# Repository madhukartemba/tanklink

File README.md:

# TankLink

Local rooftop **tank ↔ pump** control — no cloud required.

- **Phone ↔ pump:** BLE (claim/pair, On/Off, settings)
- **Tank ↔ pump:** LoRa (RA-02 / SX1278) — tank TX + pump RX done
- **Hardware:** ESP32-C3 (pump + tank), Flutter app

| Folder | Role |
| --- | --- |
| [`pump_node/`](pump_node/) | ESP32-C3 SuperMini pump (BLE GATT, starter relays, LoRa RX, schedules) |
| [`tank_node/`](tank_node/) | XIAO ESP32-C3 tank sensor (floats, LoRa TX, deep sleep) |
| [`tanklink_app/`](tanklink_app/) | Flutter app — multi-pump, slide-to-start, settings, schedules, in-app updates |
| [`components/tanklink_lora/`](components/tanklink_lora/) | Shared SX1278 driver and LoRa packet format |

**Pin maps (both boards):** [`docs/PINMAPS.md`](docs/PINMAPS.md)  
**BLE + LoRa byte layouts:** [`docs/PROTOCOL.md`](docs/PROTOCOL.md)  
**Build and flash:** [`docs/firmware-build-setup.md`](docs/firmware-build-setup.md)  
**Settings and pins to change:** [`docs/CONFIGURATION.md`](docs/CONFIGURATION.md)  
**Working on this repo with an agent:** [`AGENTS.md`](AGENTS.md)  
**Tank LED error codes:** [`docs/ERROR_CODES.md`](docs/ERROR_CODES.md)

## Quick start

### Firmware (ESP-IDF)

Built with **ESP-IDF v6.1.0** (tag [`v6.1`](https://github.com/espressif/esp-idf/releases/tag/v6.1), commit `fff9895c`). New computer? Follow [`docs/firmware-build-setup.md`](docs/firmware-build-setup.md). To change pins or timings, see [`docs/CONFIGURATION.md`](docs/CONFIGURATION.md).

```bash
. "$HOME/esp/esp-idf/export.sh"
cd pump_node
idf.py set-target esp32c3
idf.py build
idf.py -p /dev/cu.usbmodemXXXX flash monitor
```

Hold the pump **button** ~5 s to enter BLE pairing. Advertise name is `TankLink-XXXX` (MAC suffix).

After adding the pump in the app, set **Starter → two-button**. A new or factory-reset pump defaults to "none" and won't pulse the relays.

`idf.py erase-flash` clears NVS pairing.

See [`pump_node/README.md`](pump_node/README.md) for GATT notes.

### App (Flutter)

Flutter 3.50, JDK 17, Android SDK. See [`docs/firmware-build-setup.md`](docs/firmware-build-setup.md#8-build-the-app).

```bash
cd tanklink_app
flutter pub get
flutter run
```

## Firmware updates (BLE OTA)

Pump firmware can be updated from the app over BLE (dual OTA partitions).

1. Bump `TANKLINK_FW_VERSION` and build `pump_node`
2. Publish a GitHub release tagged `pump-vX.Y.Z` with `pump_node.bin` + `firmware-manifest.json`
3. See [`docs/firmware-release.md`](docs/firmware-release.md) and `./scripts/make_pump_manifest.sh`

First flash after the OTA partition change must be over **USB**. Later updates use the app.

## Status (high level)

- [x] BLE claim / auth / multi-pump
- [x] Pump On/Off + auto-off + buzzer settings
- [x] NeoPixel status + slide-to-start UI
- [x] BLE OTA + GitHub Releases check
- [x] Starter relays (GPIO0/1, active-low) + single button
- [x] Tank node floats + LoRa TX + deep sleep / heartbeat
- [x] Pump LoRa RX + tank auto-pair (app → BLE → LoRa PAIR)
- [x] Daily fill schedules (clock set from the phone)
- [x] Second float: almost-empty sensor or a second tank
- [x] Up to 4 tank sensors per pump (up to 8 tanks), one selected tank filled at a time
- [x] DS3231 RTC: schedules and the tank's last-seen time survive a restart
- [x] Tank solar: 5 V panel on VIN charges the LiPo through the XIAO charger; the app shows the battery trend
- [x] Fill history: the last 200 fills, how long each took and why it stopped
- [x] Fill when low (both floats) and water and power charts

## License

Private / personal use unless otherwise noted.

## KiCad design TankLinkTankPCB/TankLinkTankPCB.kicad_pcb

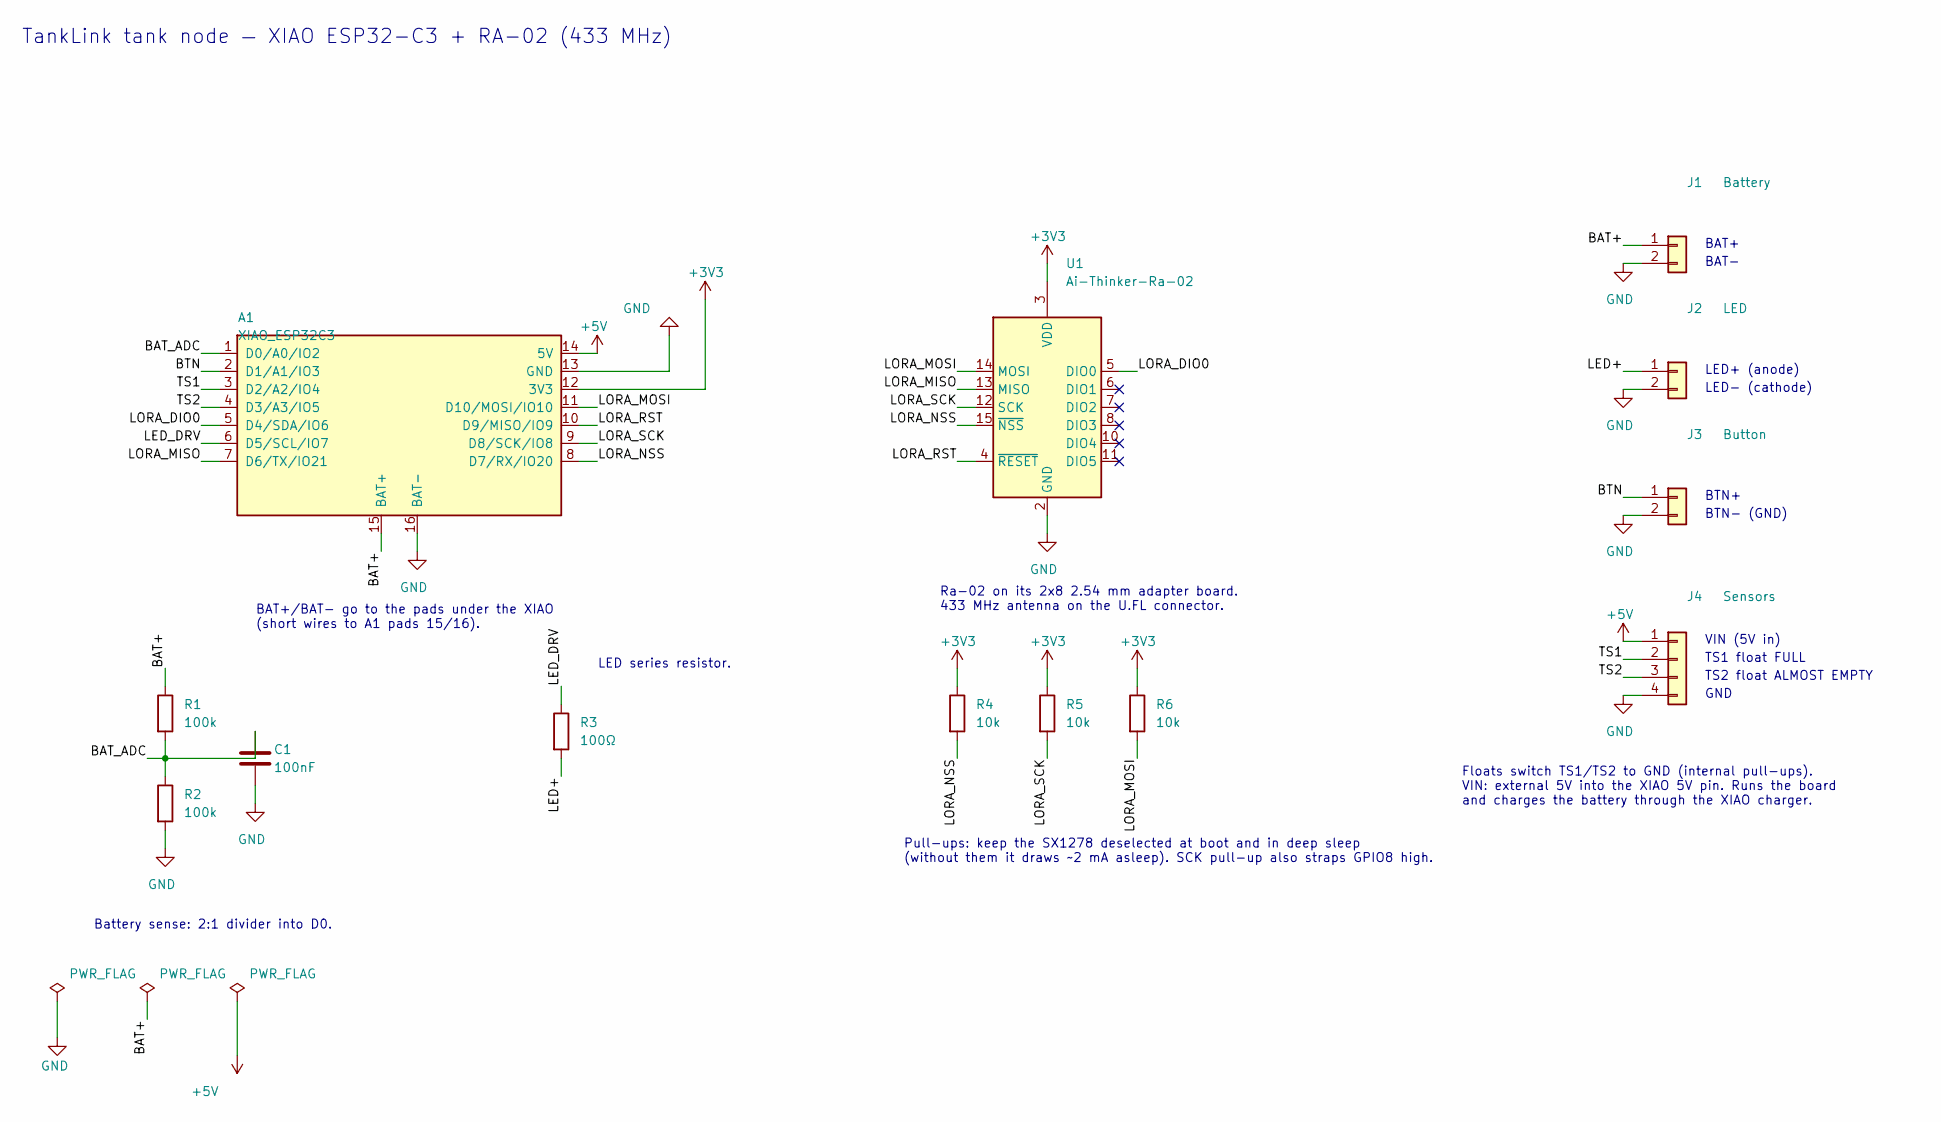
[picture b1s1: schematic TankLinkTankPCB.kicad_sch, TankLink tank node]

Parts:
A1: XIAO_ESP32C3; XIAO_ESP32C3_Socket
C1: 100nF; C_Disc_D3.0mm_W1.6mm_P2.50mm
J1: Battery; JST_PH_S2B-PH-K_1x02_P2.00mm_Horizontal
J2: LED; JST_PH_S2B-PH-K_1x02_P2.00mm_Horizontal
J3: Button; JST_PH_S2B-PH-K_1x02_P2.00mm_Horizontal
J4: Sensors; JST_PH_S4B-PH-K_1x04_P2.00mm_Horizontal
R1, R2: 100k; R_Axial_DIN0207_L6.3mm_D2.5mm_P7.62mm_Horizontal
R3: 100Ω; R_Axial_DIN0207_L6.3mm_D2.5mm_P7.62mm_Horizontal
R4, R5, R6: 10k; R_Axial_DIN0207_L6.3mm_D2.5mm_P7.62mm_Horizontal
U1: Ai-Thinker-Ra-02; Ra-02_Breakout_2x8_P2.54mm

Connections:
+3V3: A1.12 (3V3), R4.1, R5.1, R6.1, U1.3 (VDD)
+5V: A1.14 (5V), J4.1
/BAT+: A1.15 (BAT+), J1.1, R1.1
/BAT_ADC: A1.1 (D0/A0/IO2), C1.1, R1.2, R2.1
/BTN: A1.2 (D1/A1/IO3), J3.1
/LED+: J2.1, R3.2
/LED_DRV: A1.6 (D5/SCL/IO7), R3.1
/LORA_DIO0: A1.5 (D4/SDA/IO6), U1.5 (DIO0)
/LORA_MISO: A1.7 (D6/TX/IO21), U1.13 (MISO)
/LORA_MOSI: A1.11 (D10/MOSI/IO10), R6.2, U1.14 (MOSI)
/LORA_NSS: A1.8 (D7/RX/IO20), R4.2, U1.15 (~NSS)
/LORA_RST: A1.10 (D9/MISO/IO9), U1.4 (~RESET)
/LORA_SCK: A1.9 (D8/SCK/IO8), R5.2, U1.12 (SCK)
/TS1: A1.3 (D2/A2/IO4), J4.2
/TS2: A1.4 (D3/A3/IO5), J4.3
GND: A1.13 (GND), A1.16 (BAT-), C1.2, J1.2, J2.2, J3.2, J4.4, R2.2, U1.1 (GND), U1.2 (GND), U1.9 (GND), U1.16 (GND)

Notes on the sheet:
TankLink tank node — XIAO ESP32-C3 + RA-02 (433 MHz)
BAT+/BAT- go to the pads under the XIAO (short wires to A1 pads 15/16).
Ra-02 on its 2x8 2.54 mm adapter board. 433 MHz antenna on the U.FL connector.
Pull-ups: keep the SX1278 deselected at boot and in deep sleep (without them it draws ~2 mA asleep). SCK pull-up also straps GPIO8 high.
Battery sense: 2:1 divider into D0.
LED series resistor.
BAT+
BAT-
LED+ (anode)
LED- (cathode)
BTN+
BTN- (GND)
VIN (5V in)
TS1 float FULL
TS2 float ALMOST EMPTY
GND
Floats switch TS1/TS2 to GND (internal pull-ups). VIN: external 5V into the XIAO 5V pin. Runs the board and charges the battery through the XIAO charger.

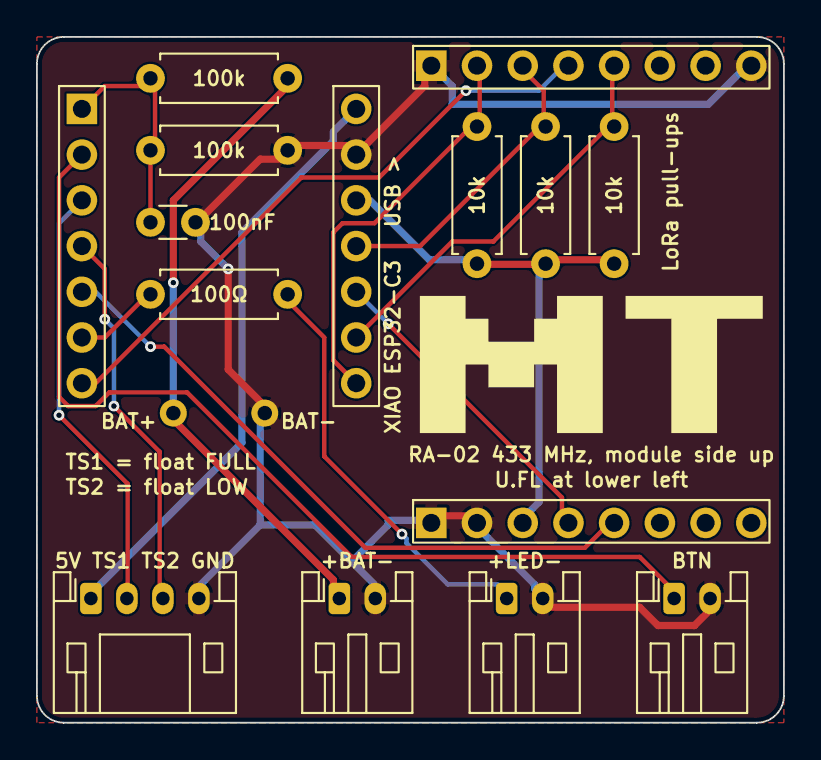
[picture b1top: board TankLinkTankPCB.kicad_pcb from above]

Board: 2 copper layers, 41.5 x 38.1 mm, 15 parts (1 on the bottom side), 16 nets.

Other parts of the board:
LOGO1, LOGO2: LOGO; MadhukarTemba_Logo

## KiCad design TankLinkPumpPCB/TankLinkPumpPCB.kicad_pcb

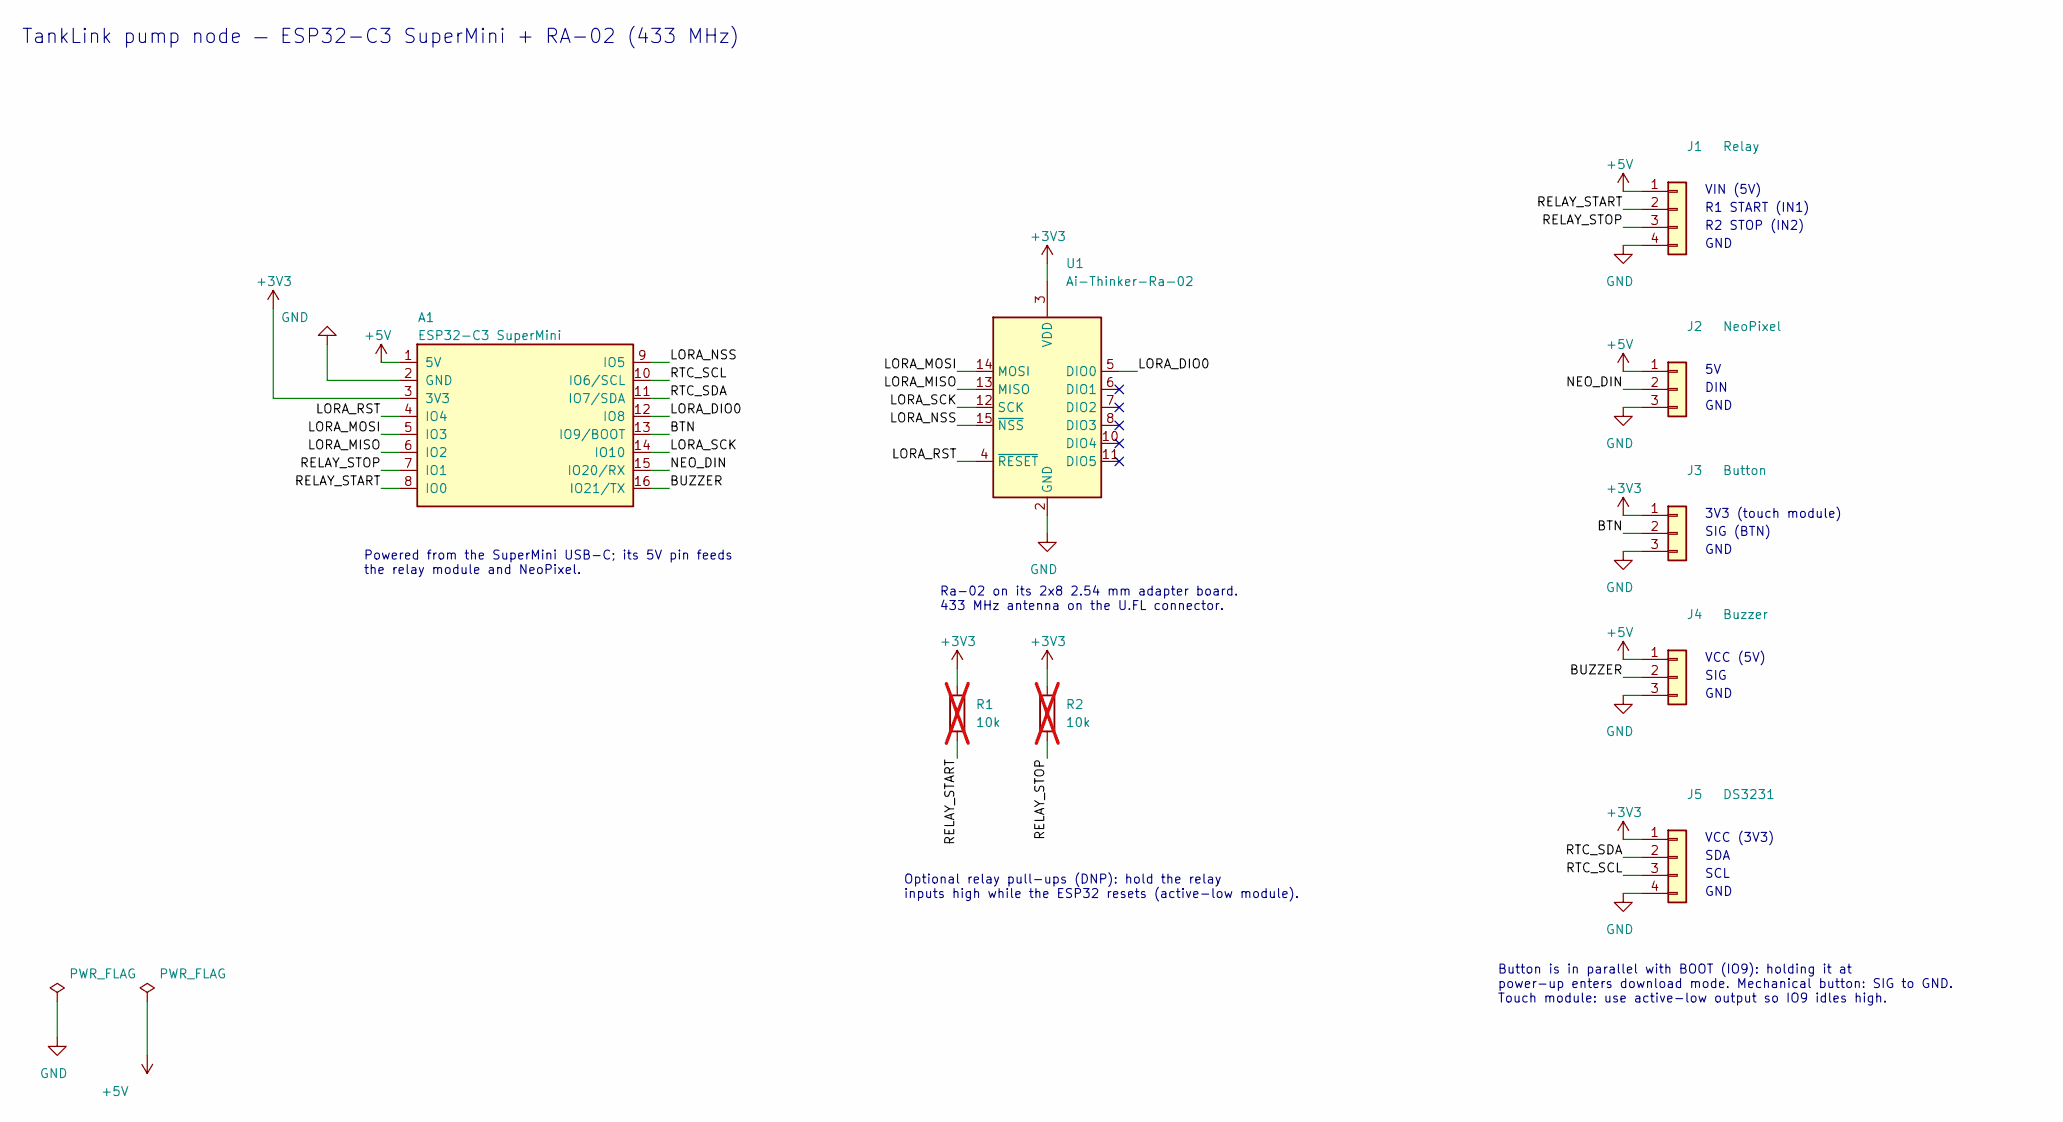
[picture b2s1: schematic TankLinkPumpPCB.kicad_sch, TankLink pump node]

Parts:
A1: ESP32-C3 SuperMini; ESP32C3_SuperMini_Socket
J1: Relay; JST_PH_S4B-PH-K_1x04_P2.00mm_Horizontal
J2: NeoPixel; JST_PH_S3B-PH-K_1x03_P2.00mm_Horizontal
J3: Button; JST_PH_S3B-PH-K_1x03_P2.00mm_Horizontal
J4: Buzzer; JST_PH_S3B-PH-K_1x03_P2.00mm_Horizontal
J5: DS3231; JST_PH_S4B-PH-K_1x04_P2.00mm_Horizontal
R1, R2: 10k; R_Axial_DIN0207_L6.3mm_D2.5mm_P7.62mm_Horizontal; not fitted
U1: Ai-Thinker-Ra-02; Ra-02_Breakout_2x8_P2.54mm

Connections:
+3V3: A1.3 (3V3), J3.1, J5.1, R1.1, R2.1, U1.3 (VDD)
+5V: A1.1 (5V), J1.1, J2.1, J4.1
/BTN: A1.13 (IO9/BOOT), J3.2
/BUZZER: A1.16 (IO21/TX), J4.2
/LORA_DIO0: A1.12 (IO8), U1.5 (DIO0)
/LORA_MISO: A1.6 (IO2), U1.13 (MISO)
/LORA_MOSI: A1.5 (IO3), U1.14 (MOSI)
/LORA_NSS: A1.9 (IO5), U1.15 (~NSS)
/LORA_RST: A1.4 (IO4), U1.4 (~RESET)
/LORA_SCK: A1.14 (IO10), U1.12 (SCK)
/NEO_DIN: A1.15 (IO20/RX), J2.2
/RELAY_START: A1.8 (IO0), J1.2, R1.2
/RELAY_STOP: A1.7 (IO1), J1.3, R2.2
/RTC_SCL: A1.10 (IO6/SCL), J5.3
/RTC_SDA: A1.11 (IO7/SDA), J5.2
GND: A1.2 (GND), J1.4, J2.3, J3.3, J4.3, J5.4, U1.1 (GND), U1.2 (GND), U1.9 (GND), U1.16 (GND)

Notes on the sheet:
TankLink pump node — ESP32-C3 SuperMini + RA-02 (433 MHz)
Powered from the SuperMini USB-C; its 5V pin feeds the relay module and NeoPixel.
Ra-02 on its 2x8 2.54 mm adapter board. 433 MHz antenna on the U.FL connector.
Optional relay pull-ups (DNP): hold the relay inputs high while the ESP32 resets (active-low module).
VIN (5V)
R1 START (IN1)
R2 STOP (IN2)
GND
DIN
3V3 (touch module)
SIG (BTN)
VCC (5V)
SIG
VCC (3V3)
SDA
SCL
Button is in parallel with BOOT (IO9): holding it at power-up enters download mode. Mechanical button: SIG to GND. Touch module: use active-low output so IO9 idles high.

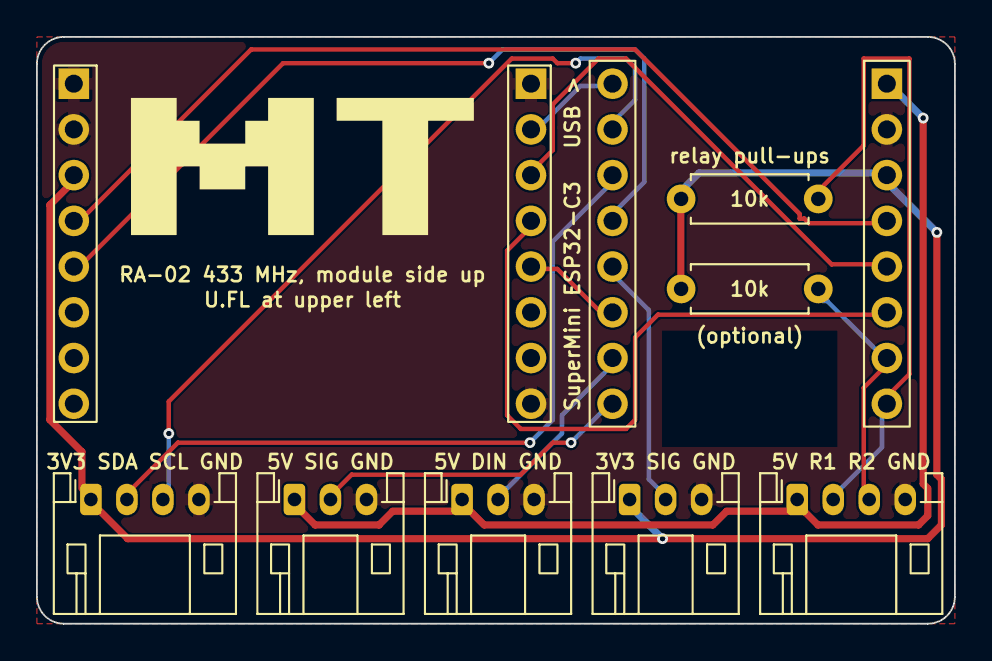
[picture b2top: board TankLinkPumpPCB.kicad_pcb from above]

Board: 2 copper layers, 51.0 x 32.6 mm, 11 parts (1 on the bottom side), 16 nets.

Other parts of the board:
LOGO1, LOGO2: LOGO; MadhukarTemba_Logo
